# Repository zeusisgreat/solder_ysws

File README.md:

# Batman_blinky_pcb

I made a pcb with a shape of batman logo with the art of guns and roses and also with a slang NASTY. In this pcb i have used 6 leds and 6 resistor with a battery holder and also with a switch and with a holding mount for the keychain.

## Schematic

## PCB

## How to build
 order the PCB & components, open up the KiCAD file and build it accordingly.

## BOM
- 1 	Battery holder
- 6	470ohms Resistor
- 1 	Push Button
- 6 LEDs

Made by Saman

Made as a part of http://solder.hackclub.com/!

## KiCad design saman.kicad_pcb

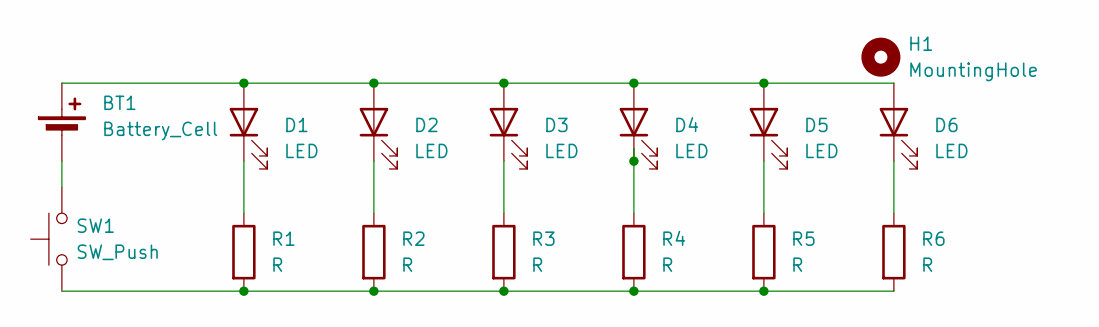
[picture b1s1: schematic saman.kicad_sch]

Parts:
BT1: Battery_Cell; BatteryHolder_Keystone_3034_1x20mm
D1, D2, D3, D4, D5, D6: LED; LED_D5.0mm
H1: MountingHole; MountingHole_5mm
R1, R2, R3, R4, R5, R6: R; R_Axial_DIN0207_L6.3mm_D2.5mm_P7.62mm_Horizontal
SW1: SW_Push; SW_PUSH_6mm

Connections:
unnamed: BT1.1 (+), D1.2 (A), D2.2 (A), D3.2 (A), D4.2 (A), D5.2 (A), D6.2 (A)
unnamed: BT1.2 (-), SW1.2
unnamed: D1.1 (K), R1.1
unnamed: D2.1 (K), R2.1
unnamed: D3.1 (K), R3.1
unnamed: D4.1 (K), R4.1
unnamed: D5.1 (K), R5.1
unnamed: D6.1 (K), R6.1
unnamed: R1.2, R2.2, R3.2, R4.2, R5.2, R6.2, SW1.1

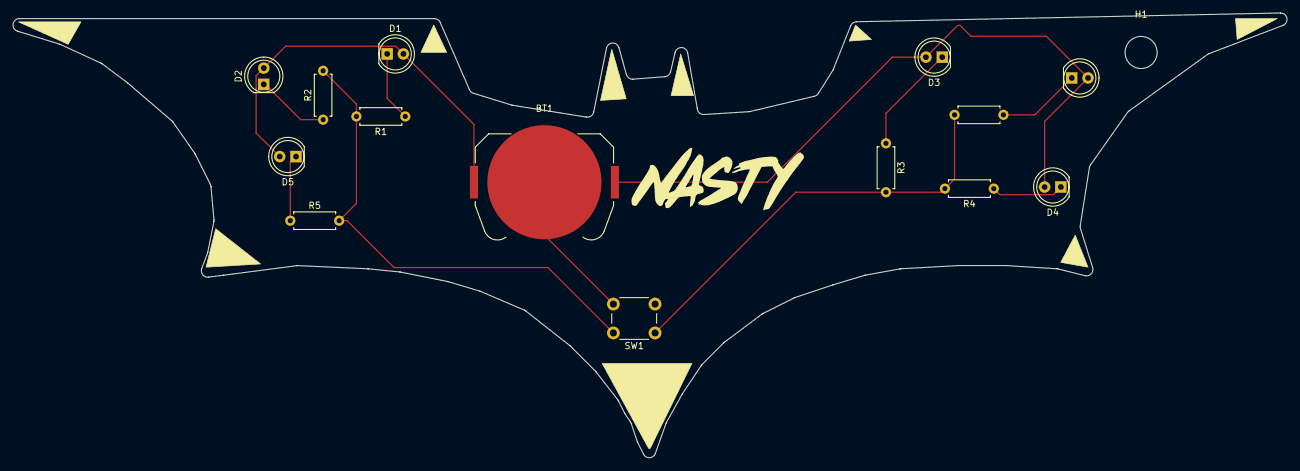
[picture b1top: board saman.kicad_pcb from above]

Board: 2 copper layers, 198.6 x 69.3 mm, 15 parts (0 on the bottom side), 9 nets.
